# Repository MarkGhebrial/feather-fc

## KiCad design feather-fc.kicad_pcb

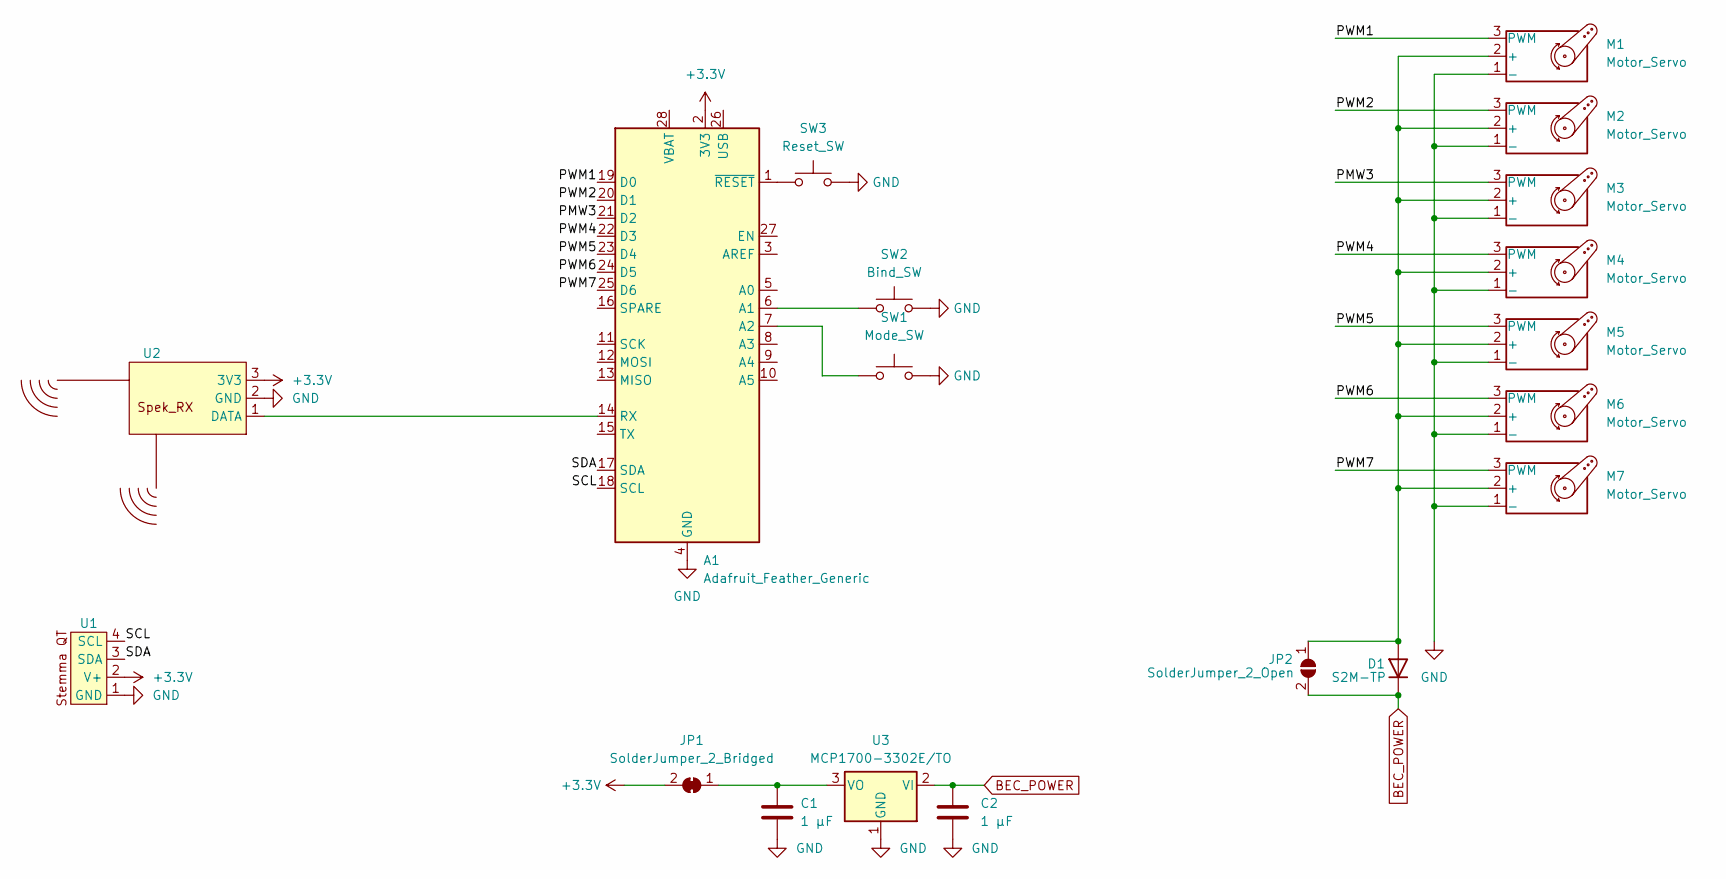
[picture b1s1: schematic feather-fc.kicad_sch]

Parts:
A1: Adafruit_Feather_Generic; Adafruit_Feather
C1, C2: 1 µF; C_1210_3225Metric
D1: S2M-TP; D_SMB
JP1: SolderJumper_2_Bridged; SolderJumper-2_P1.3mm_Bridged_RoundedPad1.0x1.5mm
JP2: SolderJumper_2_Open; SolderJumper-2_P1.3mm_Open_RoundedPad1.0x1.5mm
M1, M2, M3, M4, M5, M6, M7: Motor_Servo; PinHeader_1x03_P2.54mm_Vertical
SW1: Mode_SW; SW_PUSH_6mm
SW2: Bind_SW; SW_PUSH_6mm
SW3: Reset_SW; SW_PUSH_6mm
U1: JST_SH_SM04B-SRSS-TB_1x04-1MP_P1.00mm_Horizontal
U2: JST ZHR-3
U3: MCP1700-3302E/TO; TO-92_Inline

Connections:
+3.3V: A1.2 (3V3), JP1.2 (B), U1.2 (V+), U2.3 (3V3)
/PMW3: A1.21 (D2), M3.3 (PWM)
/PWM1: A1.19 (D0), M1.3 (PWM)
/PWM2: A1.20 (D1), M2.3 (PWM)
/PWM4: A1.22 (D3), M4.3 (PWM)
/PWM5: A1.23 (D4), M5.3 (PWM)
/PWM6: A1.24 (D5), M6.3 (PWM)
/PWM7: A1.25 (D6), M7.3 (PWM)
/SCL: A1.18 (SCL), U1.4 (SCL)
/SDA: A1.17 (SDA), U1.3 (SDA)
BEC_POWER: C2.1, D1.1 (K), JP2.2 (B), U3.2 (VI)
GND: A1.4 (GND), C1.2, C2.2, M1.1 (-), M2.1 (-), M3.1 (-), M4.1 (-), M5.1 (-), M6.1 (-), M7.1 (-), SW1.2, SW2.2, SW3.2, U1.1 (GND), U2.2 (GND), U3.1 (GND)
unnamed: A1.6 (A1), SW2.1
unnamed: A1.7 (A2), SW1.1
unnamed: A1.14 (RX), U2.1 (DATA)
unnamed: A1.1 (~RESET), SW3.1
unnamed: D1.2 (A), JP2.1 (A), M1.2 (+), M2.2 (+), M3.2 (+), M4.2 (+), M5.2 (+), M6.2 (+), M7.2 (+)
unnamed: C1.1, JP1.1 (A), U3.3 (VO)

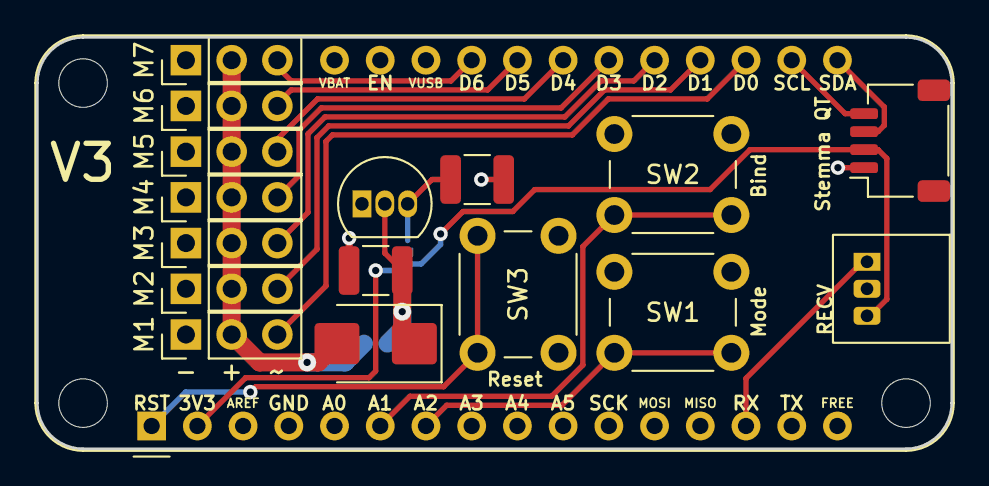
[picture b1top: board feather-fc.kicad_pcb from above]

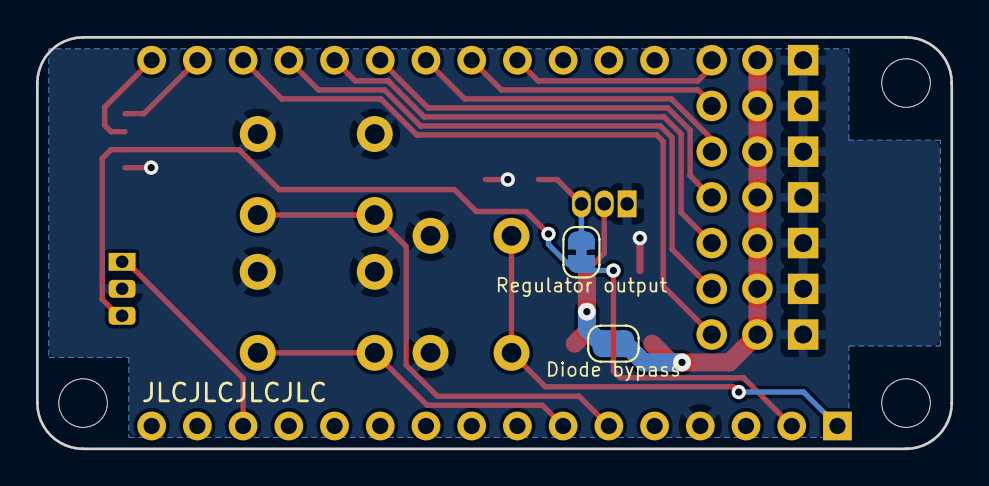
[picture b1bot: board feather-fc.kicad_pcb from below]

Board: 2 copper layers, 50.8 x 22.9 mm, 19 parts (2 on the bottom side), 18 nets.

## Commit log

2023-11-04 Add gitignore
2023-11-05 Version 2: Fix the voltage regulator wiring
2023-12-11 Version 3 layout 1
    Add reverse voltage protection diode and reset button
2023-12-11 Version 3 layout 2
2023-12-15 Verion 3 final revision
    General cleanup and rearrangement
